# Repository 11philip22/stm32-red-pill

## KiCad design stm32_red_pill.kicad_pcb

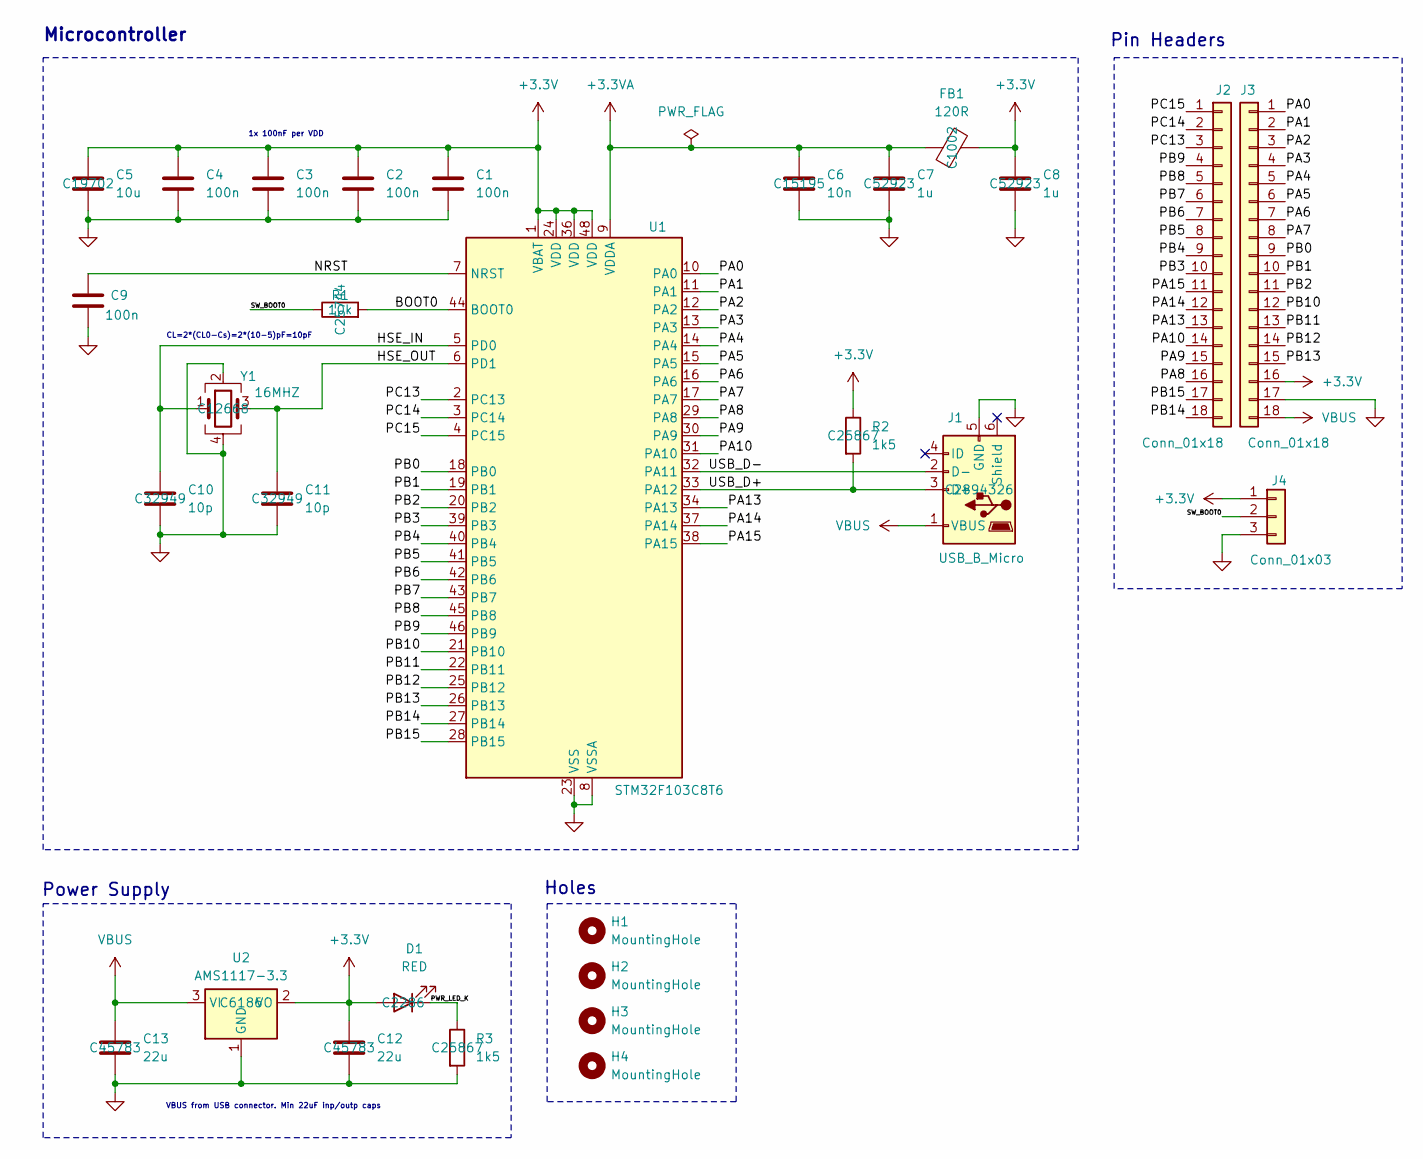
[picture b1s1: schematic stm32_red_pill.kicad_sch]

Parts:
C1, C2, C3, C4, C9: 100n; C_0402_1005Metric; LCSC C1525
C5: 10u; C_0603_1608Metric; LCSC C19702
C6: 10n; C_0402_1005Metric; LCSC C15195
C7, C8: 1u; C_0402_1005Metric; LCSC C52923
C10, C11: 10p; C_0402_1005Metric; LCSC C32949
C12, C13: 22u; C_0805_2012Metric; LCSC C45783
D1: RED; LED_0603_1608Metric; LCSC C2286
FB1: 120R; L_0603_1608Metric; LCSC C1002
H1, H2, H3, H4: MountingHole; MountingHole_2.1mm
J1: USB_B_Micro; USB_Micro-B_Wuerth_629105150521; LCSC C2894326
J2, J3: Conn_01x18; PinHeader_1x18_P2.54mm_Vertical
J4: Conn_01x03; PinHeader_1x03_P2.54mm_Vertical
R1: 10k; R_0402_1005Metric; LCSC C25744
R2, R3: 1k5; R_0402_1005Metric; LCSC C25867
U1: STM32F103C8T6; LQFP-48_7x7mm_P0.5mm; LCSC C8734
U2: AMS1117-3.3; SOT-223-3_TabPin2; LCSC C6186
Y1: 16MHZ; Crystal_SMD_3225-4Pin_3.2x2.5mm; LCSC C12668

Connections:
+3.3V: C1.1, C2.1, C3.1, C4.1, C5.1, C8.1, C12.1, D1.2 (A), FB1.2, J3.16, J4.1, R2.1, U1.1 (VBAT), U1.24 (VDD), U1.36 (VDD), U1.48 (VDD), U2.2 (VO)
+3.3VA: C6.1, C7.1, FB1.1, U1.9 (VDDA)
/BOOT0: R1.2, U1.44 (BOOT0)
/HSE_IN: C10.1, U1.5 (PD0), Y1.1
/HSE_OUT: C11.1, U1.6 (PD1), Y1.3
/NRST: C9.1, U1.7 (NRST)
/PA0: J3.1, U1.10 (PA0)
/PA1: J3.2, U1.11 (PA1)
/PA2: J3.3, U1.12 (PA2)
/PA3: J3.4, U1.13 (PA3)
/PA4: J3.5, U1.14 (PA4)
/PA5: J3.6, U1.15 (PA5)
/PA6: J3.7, U1.16 (PA6)
/PA7: J3.8, U1.17 (PA7)
/PA8: J2.16, U1.29 (PA8)
/PA9: J2.15, U1.30 (PA9)
/PA10: J2.14, U1.31 (PA10)
/PA13: J2.13, U1.34 (PA13)
/PA14: J2.12, U1.37 (PA14)
/PA15: J2.11, U1.38 (PA15)
/PB0: J3.9, U1.18 (PB0)
/PB1: J3.10, U1.19 (PB1)
/PB2: J3.11, U1.20 (PB2)
/PB3: J2.10, U1.39 (PB3)
/PB4: J2.9, U1.40 (PB4)
/PB5: J2.8, U1.41 (PB5)
/PB6: J2.7, U1.42 (PB6)
/PB7: J2.6, U1.43 (PB7)
/PB8: J2.5, U1.45 (PB8)
/PB9: J2.4, U1.46 (PB9)
/PB10: J3.12, U1.21 (PB10)
/PB11: J3.13, U1.22 (PB11)
/PB12: J3.14, U1.25 (PB12)
/PB13: J3.15, U1.26 (PB13)
/PB14: J2.18, U1.27 (PB14)
/PB15: J2.17, U1.28 (PB15)
/PC13: J2.3, U1.2 (PC13)
/PC14: J2.2, U1.3 (PC14)
/PC15: J2.1, U1.4 (PC15)
/PWR_LED_K: D1.1 (K), R3.1
/SW_BOOT0: J4.2, R1.1
/USB_D+: J1.3 (D+), R2.2, U1.33 (PA12)
/USB_D-: J1.2 (D-), U1.32 (PA11)
GND: C1.2, C2.2, C3.2, C4.2, C5.2, C6.2, C7.2, C8.2, C9.2, C10.2, C11.2, C12.2, C13.2, J1.5 (GND), J3.17, J4.3, R3.2, U1.8 (VSSA), U1.23 (VSS), U1.35 (VSS), U1.47 (VSS), U2.1 (GND), Y1.2, Y1.4
VBUS: C13.1, J1.1 (VBUS), J3.18, U2.3 (VI)

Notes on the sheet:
VBUS from USB connector. Min 22uF inp/outp caps
Power Supply
1x 100nF per VDD
Microcontroller
CL=2*(CL0-Cs)=2*(10-5)pF=10pF
Holes
Pin Headers

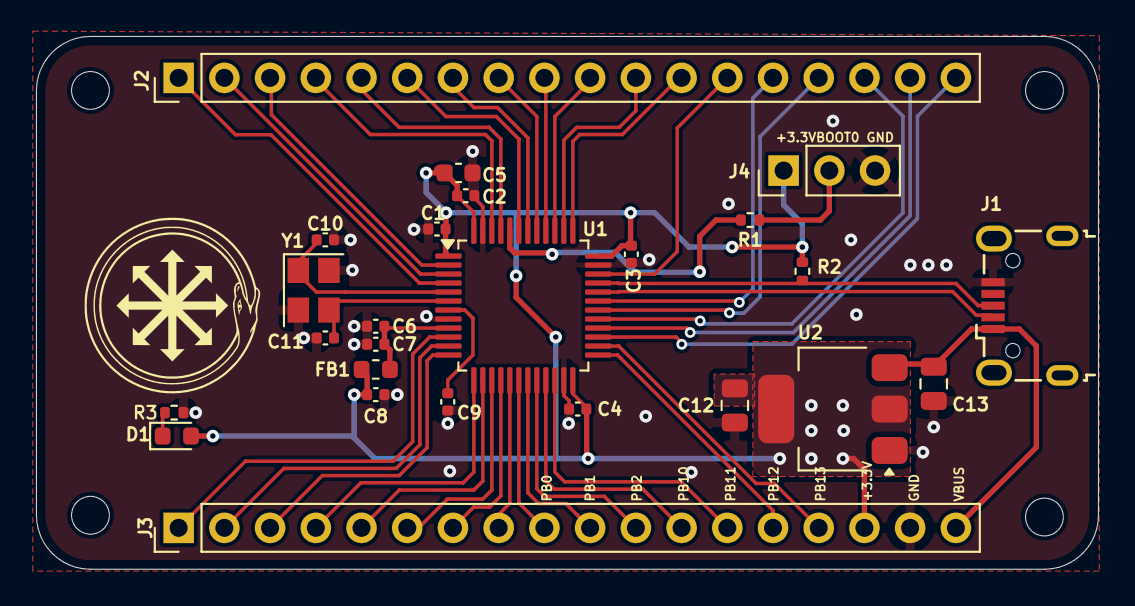
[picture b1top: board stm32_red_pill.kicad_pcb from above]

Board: 2 copper layers, 59.0 x 29.6 mm, 29 parts (0 on the bottom side), 45 nets.

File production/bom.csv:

Designator,Footprint,Quantity,Value,LCSC Part #
"C1, C2, C3, C4, C9",0402,5,100n,C1525
"C10, C11",0402,2,10p,C32949
"C12, C13",0805,2,22u,C45783
C5,0603,1,10u,C19702
C6,0402,1,10n,C15195
"C7, C8",0402,2,1u,C52923
D1,0603,1,RED,C2286
FB1,0603,1,120R,C1002
J1,USB_Micro-B_Wuerth_629105150521,1,USB_B_Micro,C2894326
"J2, J3",PinHeader_1x18_P2.54mm_Vertical,2,Conn_01x18,
J4,PinHeader_1x03_P2.54mm_Vertical,1,Conn_01x03,
R1,0402,1,10k,C25744
"R2, R3",0402,2,1k5,C25867
U1,LQFP-48_7x7mm_P0.5mm,1,STM32F103C8T6,C8734
U2,SOT-223-3_TabPin2,1,AMS1117-3.3,C6186
Y1,Crystal_SMD_3225-4Pin_3.2x2.5mm,1,16MHZ,C12668

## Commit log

2025-03-27 initial
2025-04-04 update transformer
2025-04-04 cleanup
2025-04-04 update BOM
2025-04-04 add bom datasheet
2025-04-04 remove backups
2025-04-27 update gitignore
2025-04-27 4 layer design
2025-08-11 test
2025-10-03 2 layer
2025-10-11 yes?
2025-10-11 lib submodule
2025-10-11 LCSC
